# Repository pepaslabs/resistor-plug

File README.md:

# resistor-plug
A small board for a single precision resistor, which uses machine-pin headers for a 4-wire connection.

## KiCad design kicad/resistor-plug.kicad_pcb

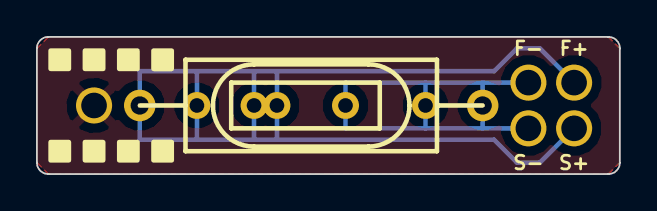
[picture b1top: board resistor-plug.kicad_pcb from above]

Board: 2 copper layers, 32.4 x 7.6 mm, 7 parts (0 on the bottom side), 2 nets.

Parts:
P1, P2, P3, P4, P5: CONN_1X1; 1pin_056_079
R1: R; R_BOX_HERMETIC_AXIAL_05_PL
R2: R; R_AXIAL_WW_069A_075_PL

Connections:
unnamed: P3.1, P5.1, R1.2, R2.2
unnamed: P2.1, P4.1, R1.1, R2.1

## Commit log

2018-04-30 adding flood fill
2018-05-04 v1.1
2018-05-04 board shots
